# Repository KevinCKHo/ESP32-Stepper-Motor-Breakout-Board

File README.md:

# ESP32 Stepper Motor Breakout Board

A Wi-Fi controlled, 4-axis stepper motor controller built around an ESP32 on a custom breakout PCB. It was designed to drive a motorized microscope stage (the *Microscope Stage Mover*). 

The ESP32 creates its own Wi-Fi access point and serves a web dashboard. From the dashboard you can jog each axis with sliders, trigger an emergency stop, and watch temperature and humidity live.

## Repository layout
| Folder | Contents |
|---|---|
| [`firmware/`](firmware) | PlatformIO project for the ESP32 (Arduino framework) |
| [`hardware/`](hardware) | KiCad 10 project for the *ESP32 Stepper Breakout Board* (schematic, PCB) |
| [`hardware/gerbers/`](hardware/gerbers) | Gerber and drill files (rev V1.1), ready to upload to a PCB fab |
| [`docs/images/`](docs/images) | Pinout, render, and board photos |

## Features
- Up to 4 stepper axes (X, Y, Z plus an optional 4th axis enabled from the UI) using Pololu-style **MP6500** driver carriers
- Variable speed and direction for each axis through slider control in the web UI
- 6 limit switches (X/Y/Z min and max) that stop motion in the triggered direction
- Software emergency stop
- **Thermal stop**: a DHT11 sensor halts all motors above 40 °C
- RGB status LED
- 5–24 V DC motor supply input on a screw terminal

## Hardware: ESP32 Stepper Breakout Board (V1.1)
An 85 × 110 mm, 2-layer board.

| JLCPCB render | Bare PCB |
|---|---|
|  |  |

**Main connectors**
| Ref | Function |
|---|---|
| J7, J8 | ESP32 DevKit (30-pin) sockets |
| J9–J16 | 4 × MP6500 driver sockets (Motor 1 X, Motor 2 Y, Motor 3 Z, Motor 4) |
| J3–J6 | Motor outputs (A2 A1 B1 B2) |
| C1–C4 | Bulk capacitors on VMOT for each driver |
| J2 | Motor power, 5–24 V DC |
| J1 | 12-way limit-switch terminal (switch to GND) |
| J17 | RGB LED (B R G −) with 220 Ω resistors R5–R7 |
| J18 | Temperature sensor (DHT11) |
| J19 | Serial COM (RX TX GND) |
| J20 | I²C display (SSD1315) |

R1–R4 are 10 kΩ pull-ups for limit inputs on GPIO 34/35/36/39. Those pins have no internal pull-ups.

### ESP32 pin map

| Function | GPIO |
|---|---|
| Motor 1 (X): STEP / DIR | 27 / 14 |
| Motor 2 (Y): STEP / DIR | 25 / 26 |
| Motor 3 (Z): STEP / DIR | 19 / 18 |
| Motor 4: STEP / DIR | 32 / 33 |
| X MIN / X MAX | 34 / 35 |
| Y MIN / Y MAX | 36 (SVP) / 39 (SVN) |
| Z MIN / Z MAX | 23 / 22 |
| RGB LED: R / G / B | 16 / 17 / 4 |
| DHT11 data | 21 |
| I²C display SDA / SCL | 21 / 22 (shared with DHT11 and Z MAX) |

## Bill of materials
Also available as [`docs/BOM.csv`](docs/BOM.csv).

| Qty | Ref | Part | MPN / Source |
|---:|---|---|---|
| 1 | J7, J8 | ESP32 ESP-32D development board (30-pin DevKit) | [Amazon](https://www.amazon.com/dp/B0C8HDDNLV) |
| 4 | J9–J16 | MP6500 stepper motor driver carrier | [Pololu #2968](https://www.pololu.com/product/2968) |
| 1 | J18 | Keyes DHT11 temperature & humidity module | — |
| 1 | J17 | Keyes KY-009 3-colour RGB LED module | — |
| 4 | C1–C4 | 100 µF 50 V electrolytic capacitor | — |
| 4 | R1–R4 | 10 kΩ 1% ¼ W, 1206 (limit-switch pull-ups) | Stackpole RMCF1206FT10K0 |
| 3 | R5–R7 | 220 Ω 1% ¼ W, 1206 (RGB LED) | Stackpole RMCF1206FT220R |
| 1 | J1 | Terminal block, 12-pos, 5 mm, side entry | Phoenix Contact 1715129 |
| 1 | J2 | Terminal block, 2-pos, 5 mm, side entry | Phoenix Contact 1715022 |
| 2 | J7, J8 | Female header 1×19, 2.54 mm (ESP32 socket) | — |
| 8 | J9–J16 | Female header 1×8, 2.54 mm (driver sockets) | — |
| 2 | J17, J20 | Female header 1×4, 2.54 mm (RGB / display) | — |
| 2 | J18, J19 | Female header 1×3, 2.54 mm (temp sensor / COM) | — |
| 4 | J3–J6 | Male pin header 1×4, 2.54 mm (motor outputs) | — |

Optional: SSD1315 0.96" I²C OLED display on J20.

## Firmware
Built with [PlatformIO](https://platformio.org/) (VS Code extension).

1. Open the `firmware/` folder in VS Code with PlatformIO installed.
2. Connect the ESP32 over USB and click **Upload**.
3. On your phone or PC, join the Wi-Fi network **`ESP32-Stepper-System2`**. The password is set in `src/main.cpp`; change it before you deploy.
4. Browse to **http://192.168.4.1** to open the control dashboard.

Libraries (installed automatically): Adafruit DHT sensor library, Adafruit Unified Sensor.

## Ordering the PCB
Upload `hardware/gerbers/ESP32 Stepper break out board V1.1.zip` to JLCPCB, PCBWay, or any other fab. Default 2-layer, 1.6 mm settings are fine.

## Author
Kevin C.K. Ho, BLANKTRACE © 2026

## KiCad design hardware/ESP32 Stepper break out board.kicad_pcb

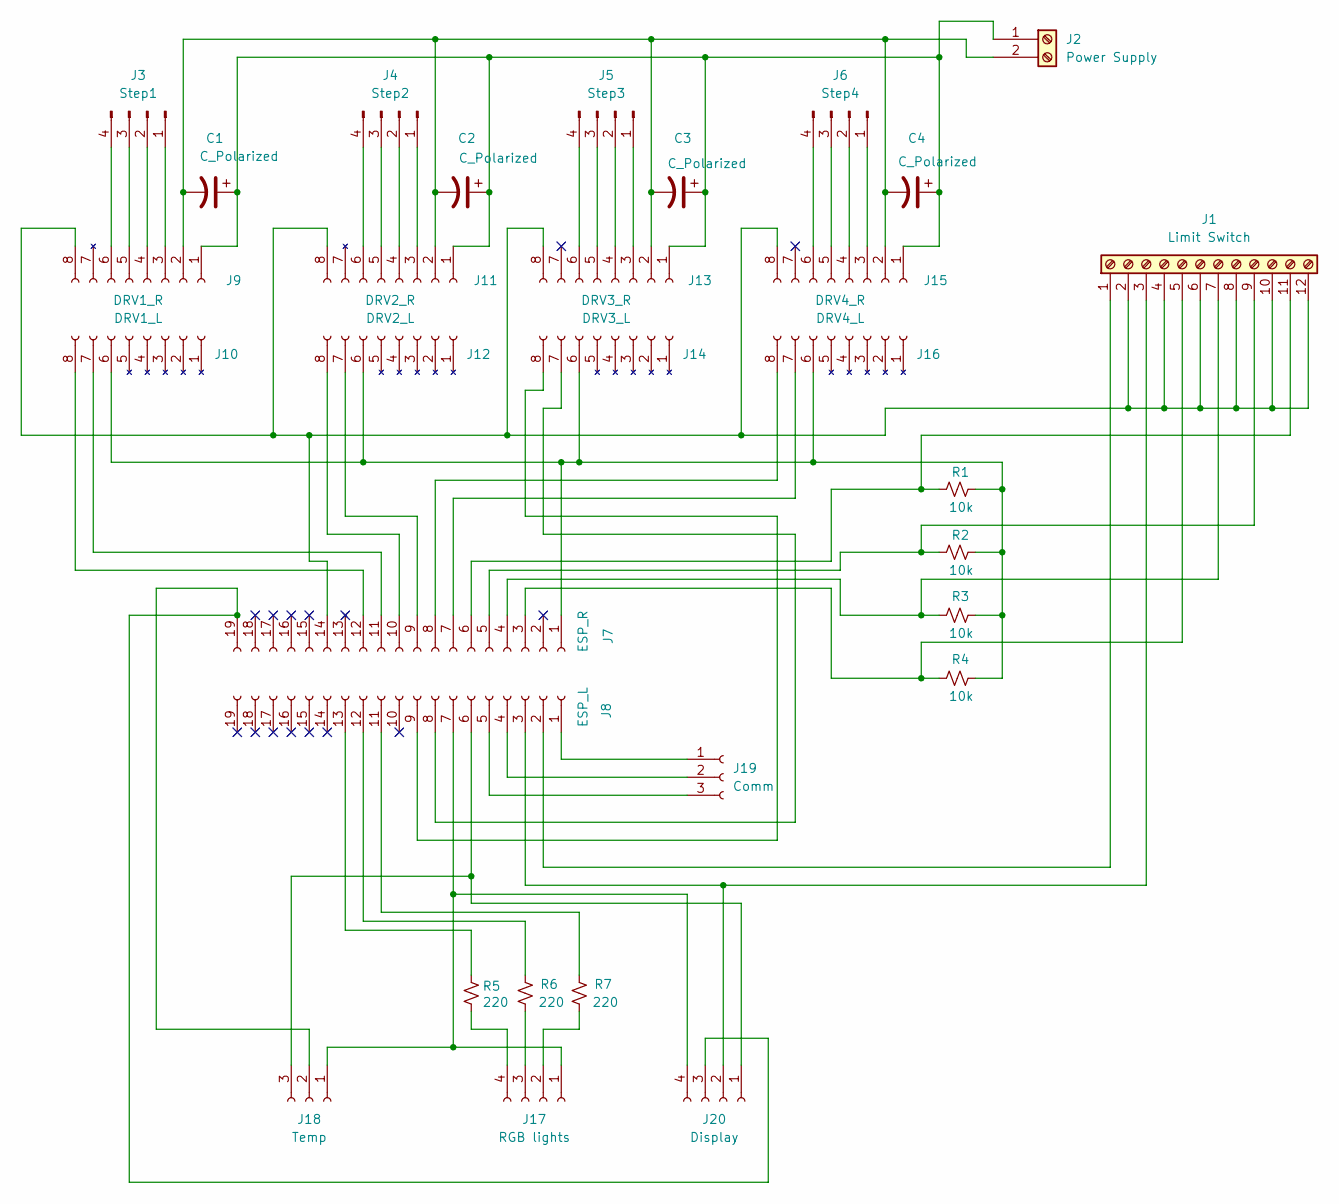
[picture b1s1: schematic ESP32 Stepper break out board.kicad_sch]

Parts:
C1, C2, C3, C4: C_Polarized; CP_Radial_D8.0mm_P3.50mm
J1: Limit Switch; TerminalBlock_Phoenix_MKDS-1,5-12_1x12_P5.00mm_Horizontal
J2: Power Supply; TerminalBlock_Phoenix_MKDS-1,5-2_1x02_P5.00mm_Horizontal
J3: Step1; PinHeader_1x04_P2.54mm_Vertical
J4: Step2; PinHeader_1x04_P2.54mm_Vertical
J5: Step3; PinHeader_1x04_P2.54mm_Vertical
J6: Step4; PinHeader_1x04_P2.54mm_Vertical
J7: ESP_R; PinSocket_1x19_P2.54mm_Vertical
J8: ESP_L; PinSocket_1x19_P2.54mm_Vertical
J9: DRV1_R; PinSocket_1x08_P2.54mm_Vertical
J10: DRV1_L; PinSocket_1x08_P2.54mm_Vertical
J11: DRV2_R; PinSocket_1x08_P2.54mm_Vertical
J12: DRV2_L; PinSocket_1x08_P2.54mm_Vertical
J13: DRV3_R; PinSocket_1x08_P2.54mm_Vertical
J14: DRV3_L; PinSocket_1x08_P2.54mm_Vertical
J15: DRV4_R; PinSocket_1x08_P2.54mm_Vertical
J16: DRV4_L; PinSocket_1x08_P2.54mm_Vertical
J17: RGB lights; PinSocket_1x04_P2.54mm_Vertical
J18: Temp; PinSocket_1x03_P2.54mm_Vertical
J19: Comm; PinSocket_1x03_P2.54mm_Vertical
J20: Display; PinSocket_1x04_P2.54mm_Vertical
R1, R2, R3, R4: 10k; R_1206_3216Metric_Pad1.30x1.75mm_HandSolder
R5, R6, R7: 220; R_1206_3216Metric_Pad1.30x1.75mm_HandSolder

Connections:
unnamed: J1.11 (xmax), J7.6 (P35_XMAX), R1.2
unnamed: J1.9 (xmin), J7.5 (P34_XMIN), R2.2
unnamed: J1.7 (ymax), J7.4 (SVN_YMAX), R3.2
unnamed: J1.5 (ymin), J7.3 (SVP_YMIN), R4.2
unnamed: J1.3 (zmax), J8.3 (P22_zmax), J20.2 (SCL)
unnamed: J1.1 (zmin), J8.2 (P23_zmin)
unnamed: J3.1, J9.3 (B2)
unnamed: J3.2, J9.4 (B1)
unnamed: J3.3, J9.5 (A1)
unnamed: J3.4, J9.6 (A2)
unnamed: J8.13 (P4_B), R5.1
unnamed: J8.12 (P16_R), R6.1
unnamed: J8.11 (P17_G), R7.1
unnamed: J7.12 (P14_DIR-1), J10.8 (DIR)
unnamed: J7.1 (3V3), J10.6 (SLP), J12.6 (SLP), J14.6 (SLP), J16.6 (SLP), R1.1, R2.1, R3.1, R4.1
unnamed: J7.11 (P27_STEP-1), J10.7 (STEP)
unnamed: J4.3, J11.5 (A1)
unnamed: J4.4, J11.6 (A2)
unnamed: J4.2, J11.4 (B1)
unnamed: J4.1, J11.3 (B2)
unnamed: C1.1, C2.1, C3.1, C4.1, J2.1 (GND), J9.1 (VMOT), J11.1 (VMOT), J13.1 (VMOT), J15.1 (VMOT)
unnamed: J7.10 (P26_DIR-2), J12.8 (DIR)
unnamed: J7.9 (P25_STEP-2), J12.7 (STEP)
unnamed: J5.3, J13.5 (A1)
unnamed: J5.4, J13.6 (A2)
unnamed: J5.2, J13.4 (B1)
unnamed: J5.1, J13.3 (B2)
unnamed: C1.2, C2.2, C3.2, C4.2, J2.2 (5-24V), J9.2 (GND), J11.2 (GND), J13.2 (GND), J15.2 (GND)
unnamed: J1.2 (GND), J1.4 (GND), J1.6 (GND), J1.8 (GND), J1.10 (GND), J1.12 (GND), J7.14 (GND), J9.8, J11.8 (GND), J13.8, J15.8
unnamed: J8.9 (P18_DIR-3), J14.8 (DIR)
unnamed: J8.8 (P19_STEP3), J14.7 (STEP)
unnamed: J6.3, J15.5 (A1)
unnamed: J6.4, J15.6 (A2)
unnamed: J6.2, J15.4 (B1)
unnamed: J6.1, J15.3 (B2)
unnamed: J7.8 (P33_DIR-4), J16.8 (DIR)
unnamed: J7.7 (P32_STEP-4), J16.7 (STEP)
unnamed: J8.7 (GND), J17.1 (-), J18.1 (-), J20.4 (GND)
unnamed: J17.4 (B), R5.2
unnamed: J17.2 (G), R7.2
unnamed: J17.3 (R), R6.2
unnamed: J7.19 (5V), J18.2 (5V), J20.3 (VCC)
unnamed: J8.6 (P21), J18.3 (S), J20.1 (SDA)
unnamed: J8.1 (GND), J19.1 (GND)
unnamed: J8.5 (RX), J19.3 (RX)
unnamed: J8.4 (TX), J19.2 (TX)

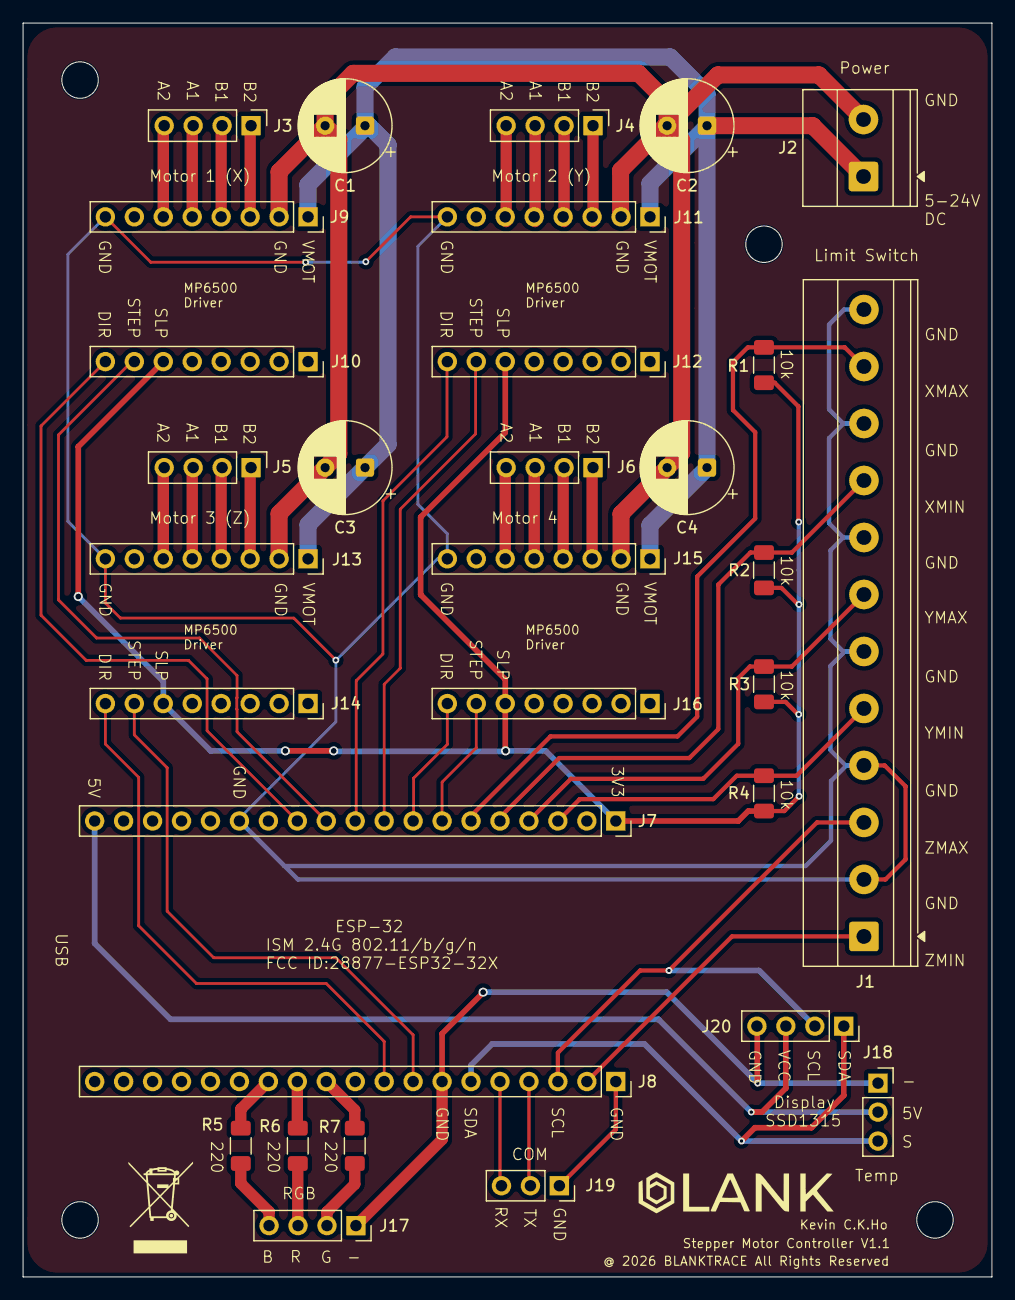
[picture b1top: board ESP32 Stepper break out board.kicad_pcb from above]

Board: 2 copper layers, 85.0 x 110.0 mm, 31 parts (0 on the bottom side), 46 nets.

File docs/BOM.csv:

Qty,Reference,Description,Manufacturer Part Number,Manufacturer,Link
1,J7 J8,ESP32 ESP-32D development board (30-pin DevKit),,,https://www.amazon.com/dp/B0C8HDDNLV
4,J9-J16,MP6500 stepper motor driver carrier,2968,Pololu,https://www.pololu.com/product/2968
1,J18,DHT11 temperature & humidity sensor module,DHT11,Keyes,
1,J17,3-colour RGB LED module,KY-009,Keyes,
4,C1-C4,100 µF 50 V electrolytic capacitor,,,
4,R1-R4,10 kΩ 1% 1/4 W resistor 1206 (limit switch pull-ups),RMCF1206FT10K0,Stackpole,
3,R5-R7,220 Ω 1% 1/4 W resistor 1206 (RGB LED),RMCF1206FT220R,Stackpole,
1,J1,Terminal block 12-pos 5 mm side entry,1715129,Phoenix Contact,
1,J2,Terminal block 2-pos 5 mm side entry,1715022,Phoenix Contact,
2,J7 J8,Female header 1x19 2.54 mm (ESP32 socket),,,
8,J9-J16,Female header 1x8 2.54 mm (driver sockets),,,
2,J17 J20,Female header 1x4 2.54 mm (RGB / display),,,
2,J18 J19,Female header 1x3 2.54 mm (temp sensor / COM),,,
4,J3-J6,Male pin header 1x4 2.54 mm (motor outputs),,,

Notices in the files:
hardware/ESP32 Stepper break out board.kicad_pcb:
@ 2026 BLANKTRACE All Rights Reserved
